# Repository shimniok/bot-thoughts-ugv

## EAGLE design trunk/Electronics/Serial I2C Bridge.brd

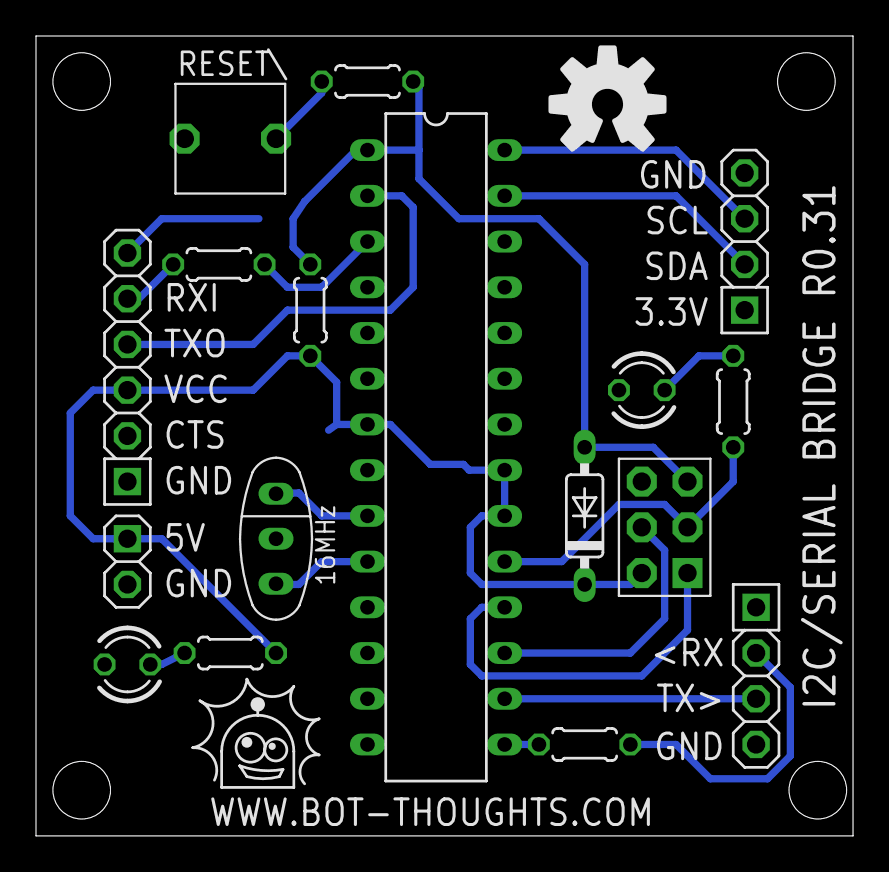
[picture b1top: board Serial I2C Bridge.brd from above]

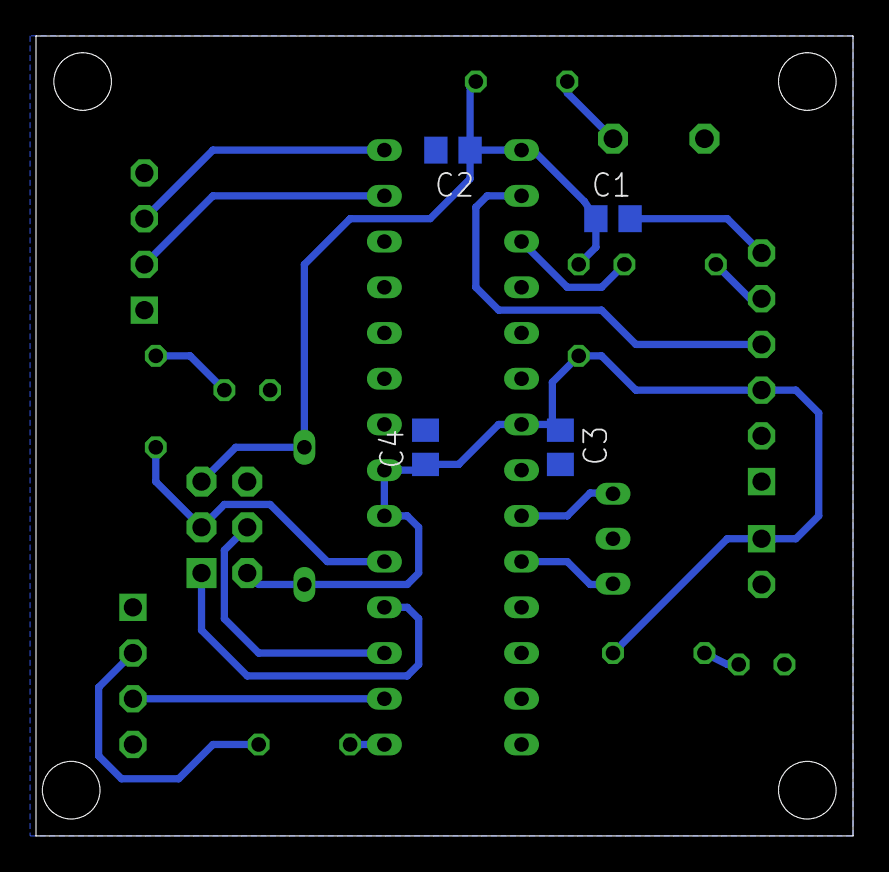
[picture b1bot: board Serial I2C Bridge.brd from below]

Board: 2 copper layers, 45.4 x 44.4 mm, 21 parts (4 on the bottom side), 20 nets.

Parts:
C1, C2, C3, C4: 0.1uF; C0805
D2: 1N4148; DO35-7
IC1: ATmega328P; DIL28-3
J1: AVRISP; CON6P2R
JP1: I2C; 1X04-S
JP2: DIAG; 1X04-S
JP4: FTDI; 1X06-S
JP5: PWR; 1X02-S
LED1, LED2: STAT1; LED3MM
Q1: 16MHz; CSTLS_G9
R1, R4, R6: 1K; 0204/5
R2, R5, R7: 330; 0204/5
S1: RESET\; EVQ11X09

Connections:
5V: C3.1, C4.1, D2.C, IC1.7, IC1.20, IC1.21, J1.2, JP4.3, JP5.1, R1.2, R7.1
!RESET: C1.1, C2.1, D2.A, IC1.1, J1.5, R1.1, R5.1
<RX: IC1.16, JP2.3
<RXD/TXO: IC1.2, JP4.4
DTR: C1.2, JP4.6
GND: C2.2, C3.2, C4.2, IC1.8, IC1.22, J1.6, JP1.4, JP2.4, JP4.1, JP5.2, LED1.K, LED2.K, Q1.2, S1.1
LV_TX>: JP2.2, R4.2
LV_TXD/RXI>: JP4.5, R6.2
MISO: IC1.18, J1.1
MOSI: IC1.17, J1.4
unnamed: IC1.9, Q1.1
unnamed: IC1.10, Q1.3
unnamed: LED1.A, R2.2
unnamed: R5.2, S1.2
unnamed: LED2.A, R7.2
RXI/TXD>: IC1.3, R6.1
SCK: IC1.19, J1.3, R2.1
SCL: IC1.28, JP1.3
SDA: IC1.27, JP1.2
TX>: IC1.15, R4.1

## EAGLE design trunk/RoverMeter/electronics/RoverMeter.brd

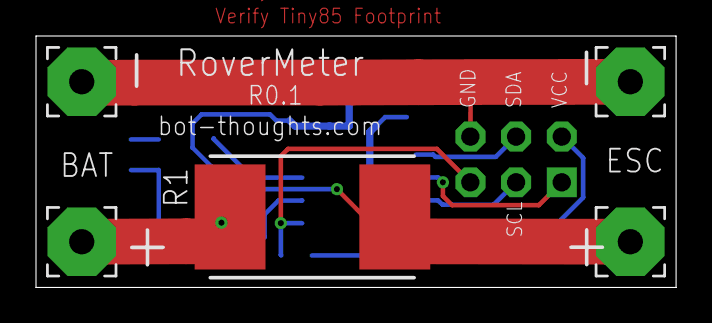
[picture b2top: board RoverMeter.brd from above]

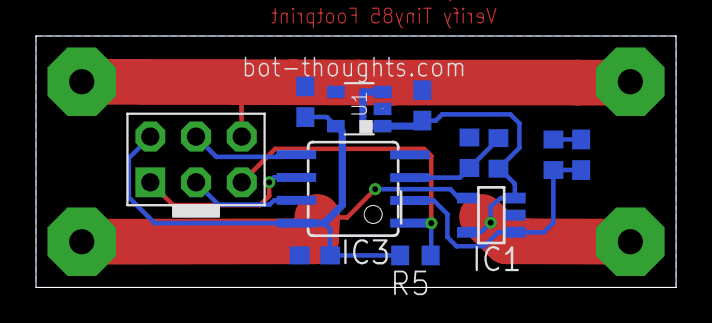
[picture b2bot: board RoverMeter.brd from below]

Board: 2 copper layers, 35.6 x 14.0 mm, 17 parts (12 on the bottom side), 10 nets.

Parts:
C1, C2: 104; C0603
C3, C4: 105; C0603
IC1: INA168; SOT23-5
IC3: TINY85; SOIC8
J1: AVRISP; CON6P2R
PAD1: BAT_V; 3,81/1,4
PAD2: BAT_G; 3,81/1,4
PAD3: ESC_V; 3,81/1,4
PAD4: ESC_G; 3,81/1,4
R1: 0.001; R4527
R2: 68k; R0603
R3: 51K; R0603
R4: 33K; R0603
R5: 10K; R0603
U1: MCP1824; SOT23-5

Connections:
5V: C2.1, C3.1, IC3.8, J1.2, R5.2, U1.5
!RESET: IC3.1, J1.5, R5.1
AMP: C1.1, IC1.1, IC3.2, R2.2
GND: C1.2, C2.2, C3.2, C4.2, IC1.2, IC3.4, J1.6, PAD2.1, PAD4.1, R2.1, R4.1, U1.2
MISO: IC3.6, J1.1
unnamed: IC1.4, PAD3.1, R1.2
SCL: IC3.7, J1.3
SDA: IC3.5, J1.4
V+: C4.1, IC1.3, IC1.5, PAD1.1, R1.1, R3.2, U1.1, U1.3
VOLT: IC3.3, R3.1, R4.2

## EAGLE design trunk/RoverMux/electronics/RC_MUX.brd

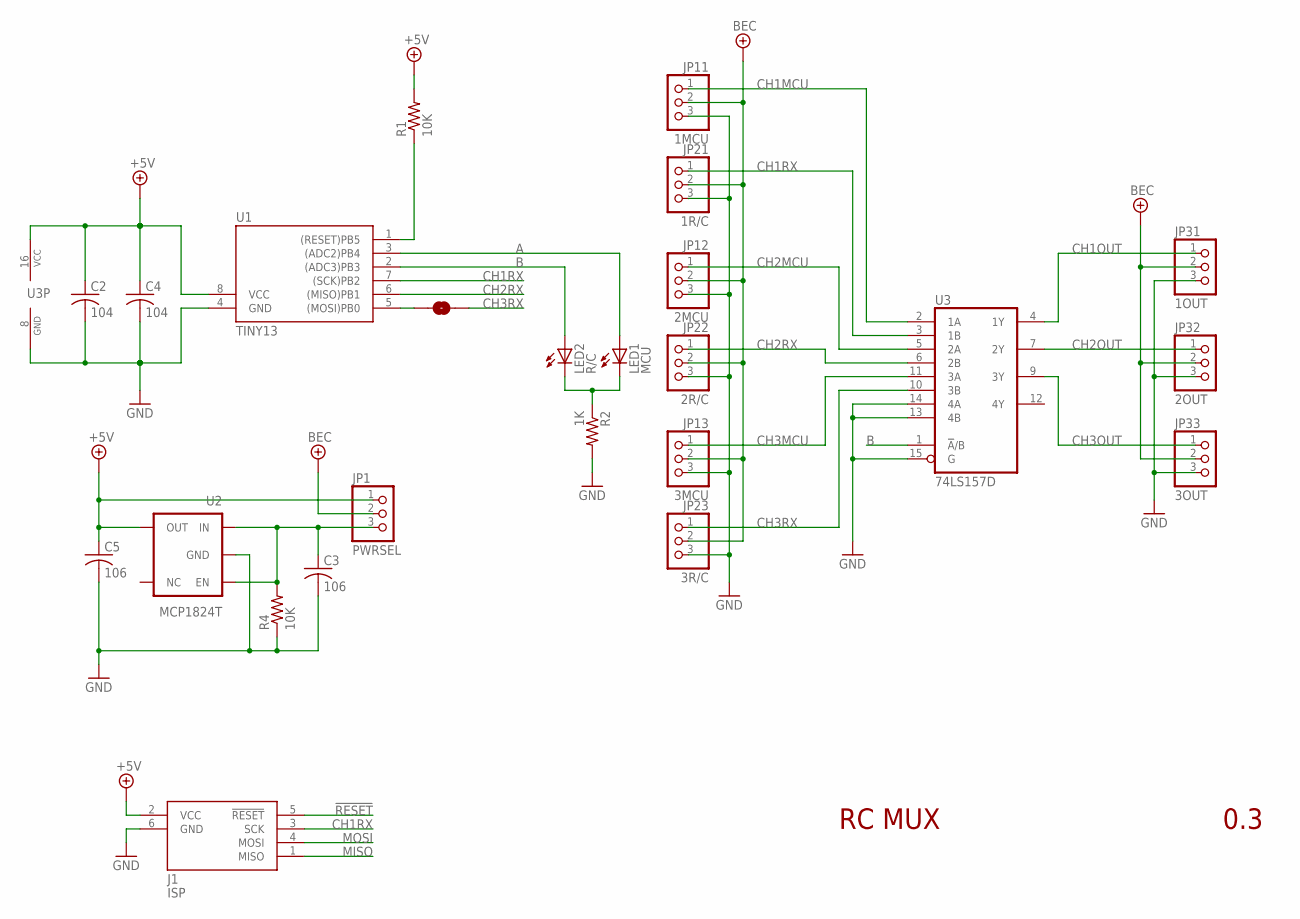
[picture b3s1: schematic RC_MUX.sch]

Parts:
C2, C4: 104; C0603; PARTNO C1608X7R1E104K080AA
C3, C5: 106; C0603; PARTNO CL10A106MP8NNNC
J1: ISP; CON6P2R
JP1: PWRSEL; 1X03M
JP11: 1MCU; 1X03-S
JP12: 2MCU; 1X03-S
JP13: 3MCU; 1X03-S
JP21: 1R/C; 1X03-S
JP22: 2R/C; 1X03-S
JP23: 3R/C; 1X03-S
JP31: 1OUT; 1X03-S
JP32: 2OUT; 1X03-S
JP33: 3OUT; 1X03-S
LED1: MCU; CHIPLED_1206; PARTNO LH N974-KN-1
LED2: R/C; CHIPLED_1206; PARTNO LG N971-KN-1
R1, R4: 10K; R0603; PARTNO 1622829-1
R2: 1K; R0603; PARTNO RC0603JR-07330RL
SJ1: CH3; SJ_2S-NOTRACE
U1: TINY13; SO08; PARTNO ATTINY13A-SSH
U2: MCP1824T; SOT23-5; PARTNO MCP1824T-5002E/OT
U3: 74LS157D; SO16; PARTNO 74HCT157D,652

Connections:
!RESET: J1.5 (!RESET), R1.1, U1.1 ((RESET)PB5)
+5V: C2.1, C4.1, C5.1, J1.2 (VCC), JP1.1, R1.2, U1.8 (VCC), U2.5 (OUT), U3.16 (VCC)
+7V: JP1.2, JP11.2, JP12.2, JP13.2, JP21.2, JP22.2, JP23.2, JP31.2, JP32.2, JP33.2
A: LED1.A, U1.3 ((ADC2)PB4)
B: LED2.A, U1.2 ((ADC3)PB3), U3.1 (!A!/B)
CH1MCU: JP11.1, U3.2 (1A)
CH1OUT: JP31.1, U3.4 (1Y)
CH1RX: J1.3 (SCK), JP21.1, U1.7 ((SCK)PB2), U3.3 (1B)
CH2MCU: JP12.1, U3.5 (2A)
CH2OUT: JP32.1, U3.7 (2Y)
CH2RX: JP22.1, U1.6 ((MISO)PB1), U3.6 (2B)
CH3MCU: JP13.1, U3.11 (3A)
CH3OUT: JP33.1, U3.9 (3Y)
CH3RX: JP23.1, SJ1.2, U3.10 (3B)
GND: C2.2, C3.2, C4.2, C5.2, J1.6 (GND), JP11.3, JP12.3, JP13.3, JP21.3, JP22.3, JP23.3, JP31.3, JP32.3, JP33.3, R2.2, R4.1, U1.4 (GND), U2.2 (GND), U3.8 (GND), U3.13 (4B), U3.14 (4A), U3.15 (G)
MISO: J1.1 (MISO)
MOSI: J1.4 (MOSI), SJ1.1, U1.5 ((MOSI)PB0)
unnamed: LED1.C, LED2.C, R2.1
REGIN: C3.1, JP1.3, R4.2, U2.1 (IN), U2.3 (EN)

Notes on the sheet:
RC MUX
0.3

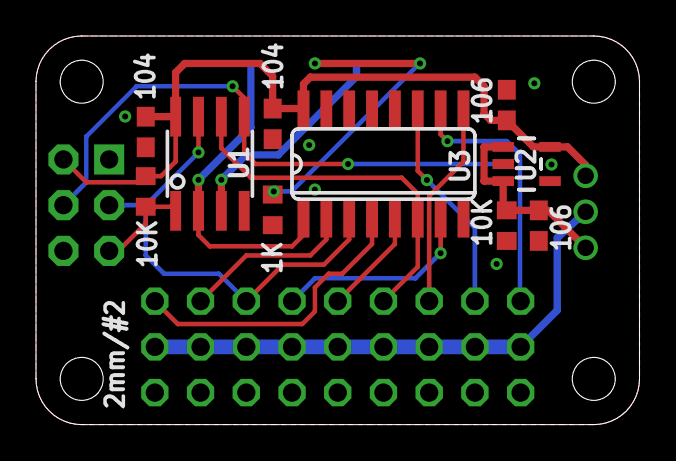
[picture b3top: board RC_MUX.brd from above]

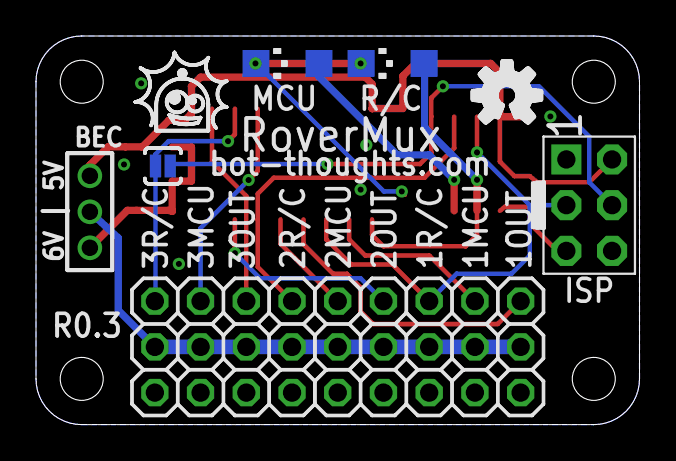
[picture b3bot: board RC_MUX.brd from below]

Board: 2 copper layers, 33.5 x 21.6 mm, 24 parts (14 on the bottom side), 18 nets.

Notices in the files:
parts and their libraries:
SparkFun: Licensing: CC v3.0 Share-Alike You are welcome to use this library for commercial purposes.
